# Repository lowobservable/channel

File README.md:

# channel

IBM parallel channel adapter.

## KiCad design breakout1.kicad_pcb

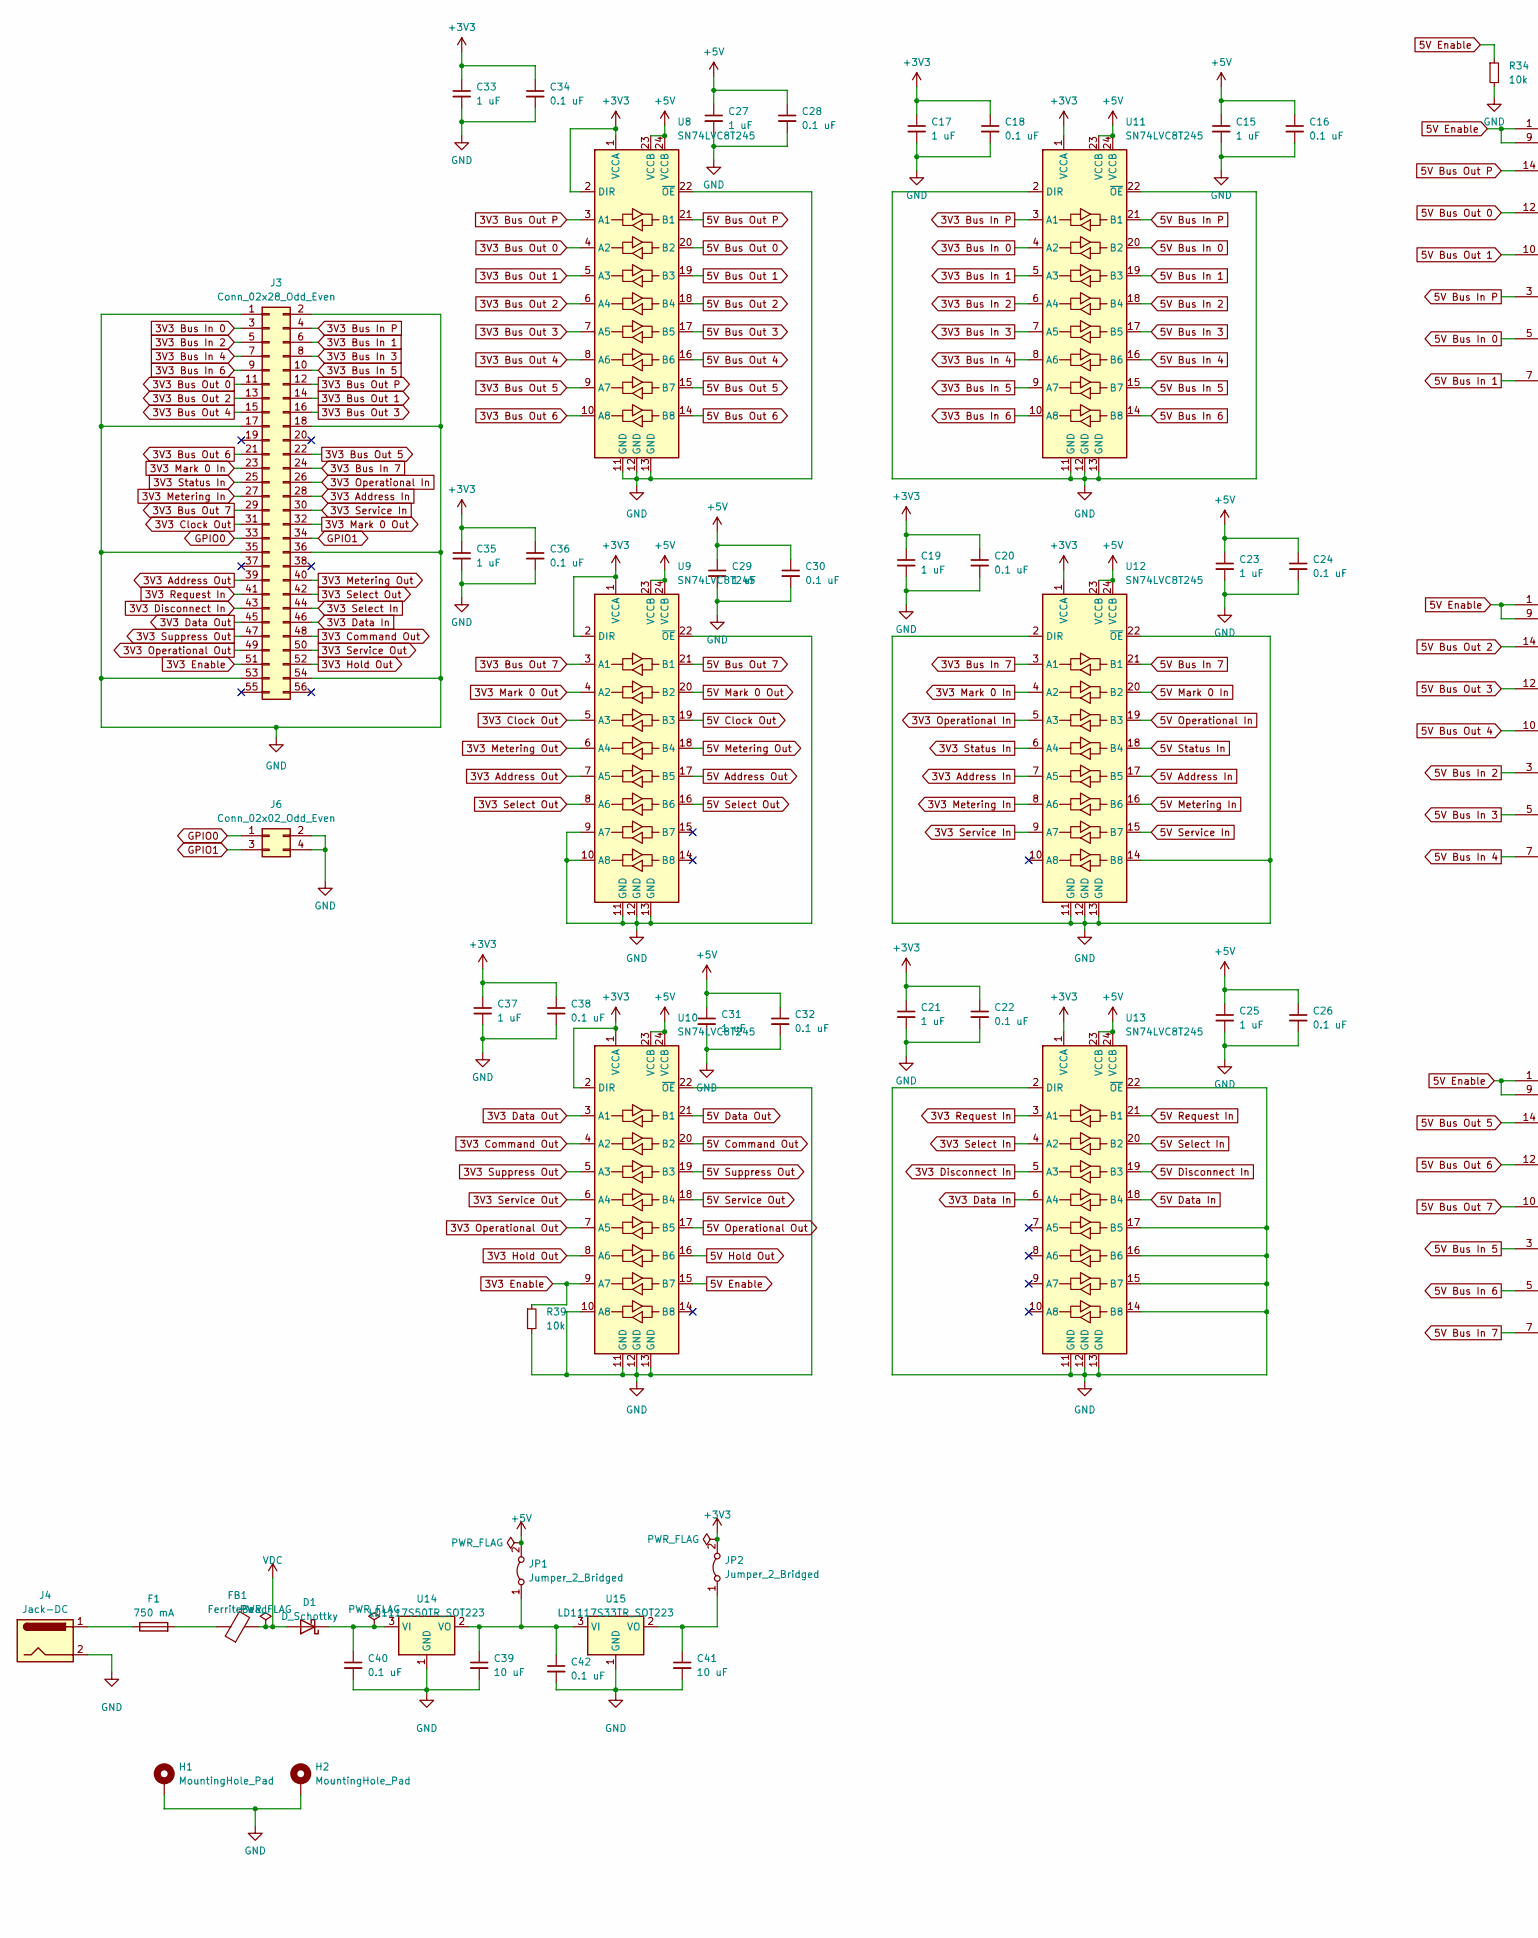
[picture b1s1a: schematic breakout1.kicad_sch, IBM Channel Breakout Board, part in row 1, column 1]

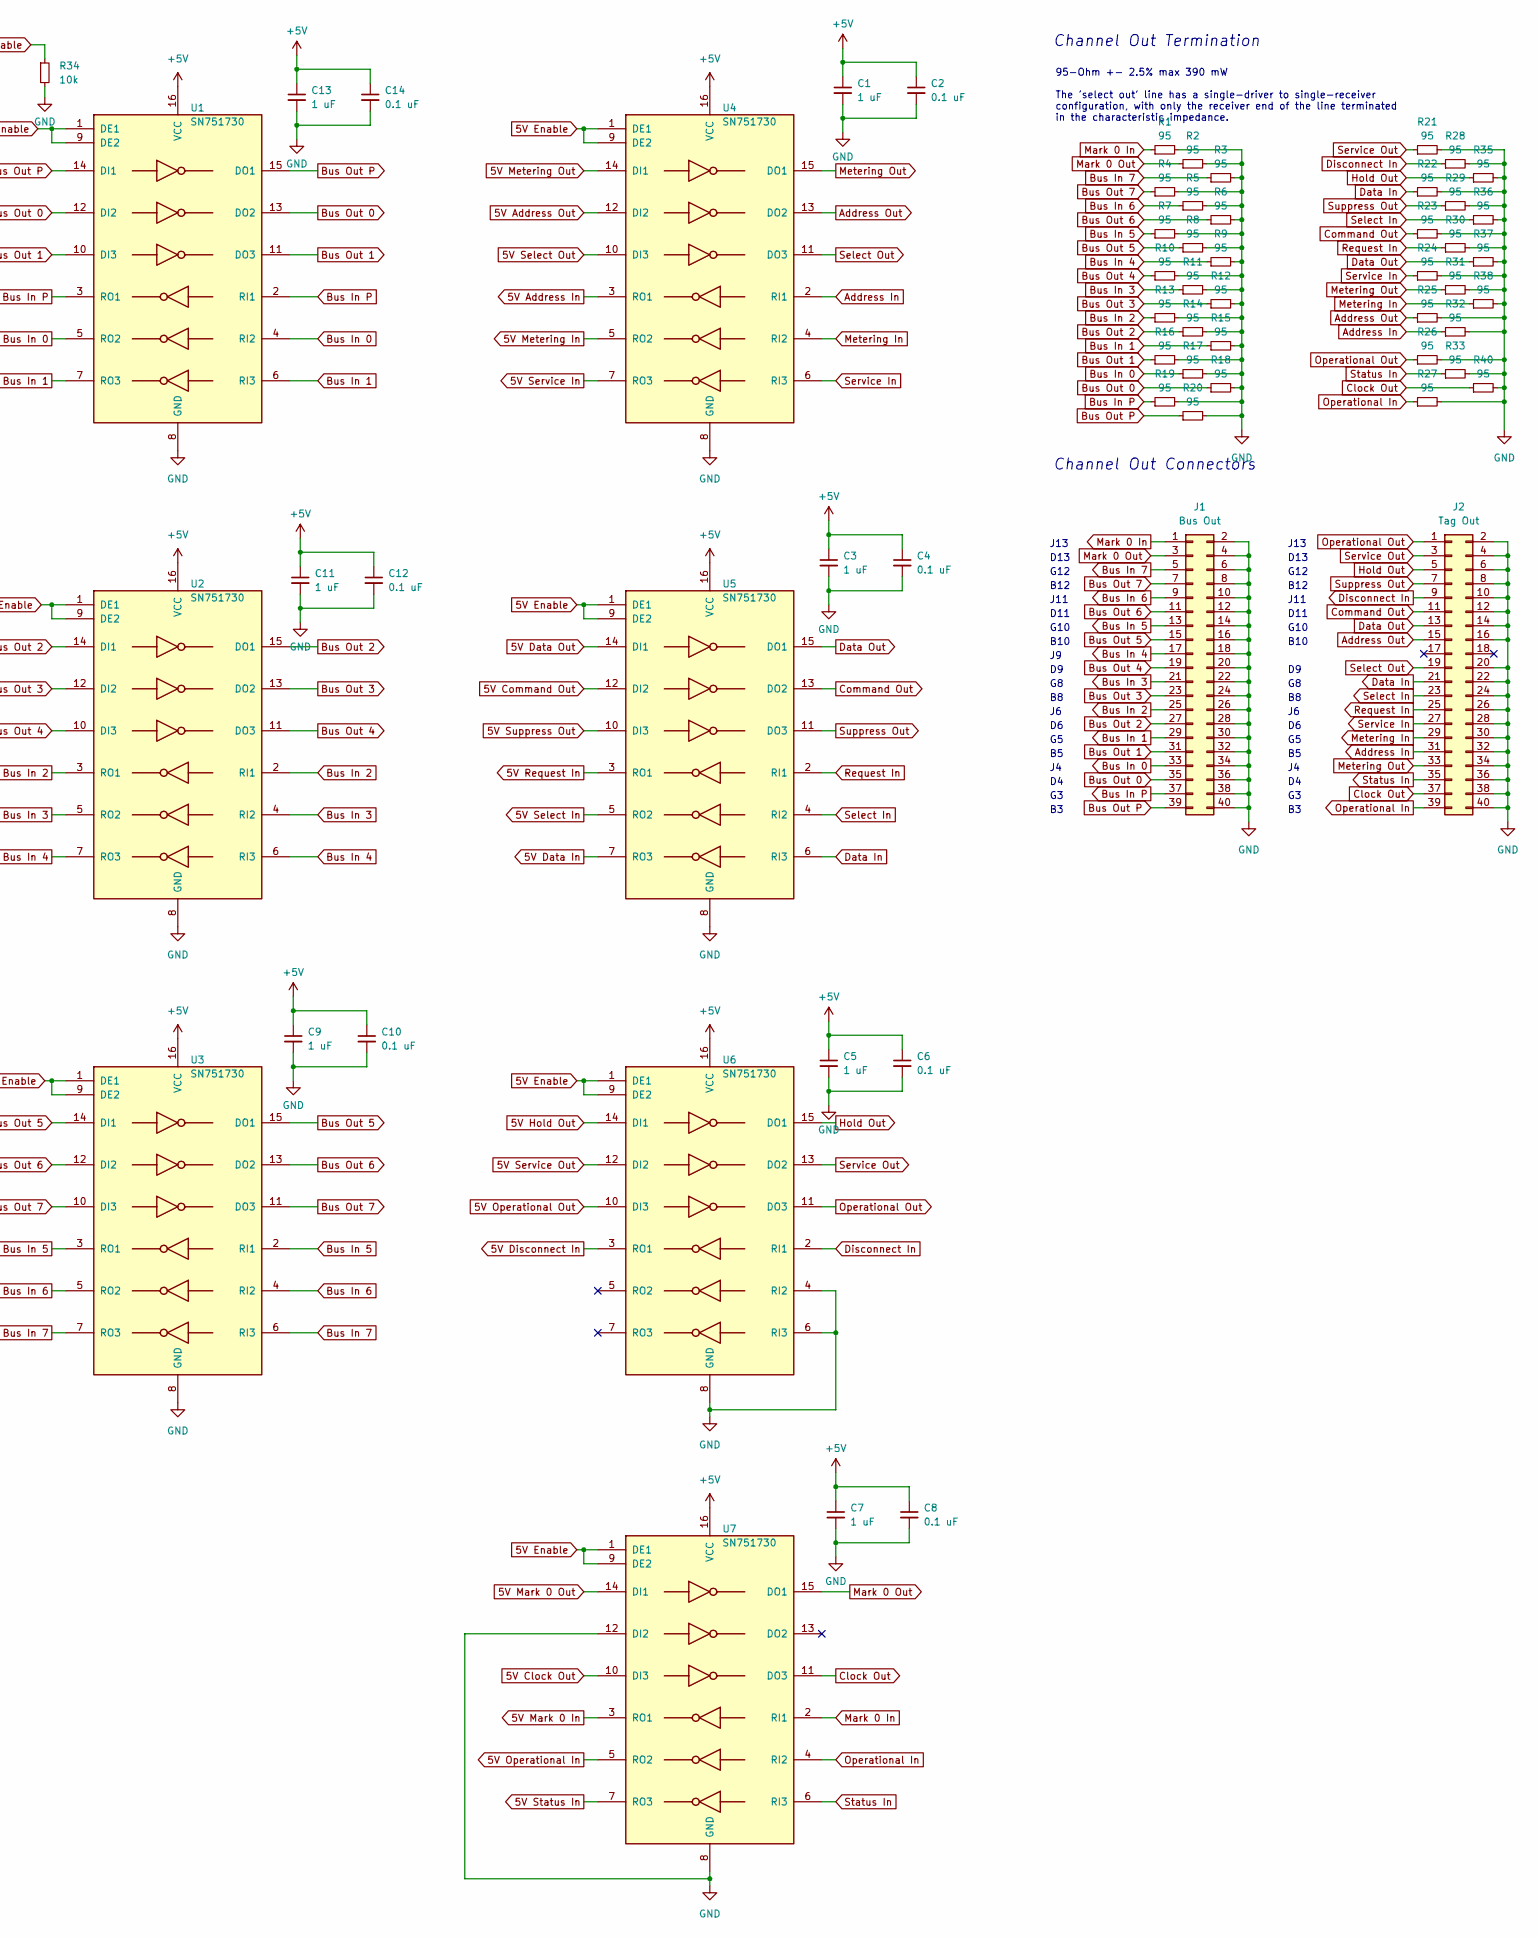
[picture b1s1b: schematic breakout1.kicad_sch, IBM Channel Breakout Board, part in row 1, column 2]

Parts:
C1, C3, C5, C7, C9, C11, C13, C15, C17, C19, C21, C23, C25, C27, C29, C31, C33, C35, C37: 1 uF; C_0603_1608Metric; Part CL10A105KP8NNNC
C2, C4, C6, C8, C10, C12, C14, C16, C18, C20, C22, C24, C26, C28, C30, C32, C34, C36, C38, C40, C42: 0.1 uF; C_0603_1608Metric; Part CL10B104KB8NNNC
C39, C41: 10 uF; C_0603_1608Metric; Part CL10A106KP8NNNC
D1: D_Schottky; D_1206_3216Metric; Part SD1206T020S1R0
F1: 750 mA; Fuse_1206_3216Metric; Part ERB-RG0R75V
FB1: FerriteBead; Fuse_1206_3216Metric; Part CZP2BPTTE101P
H1, H2: MountingHole_Pad; MountingHole_2.7mm_M2.5_ISO7380_Pad
J1: Bus Out; JST_PUD_S40B-PUDSS-1_2x20_P2.00mm_Horizontal; Part S40B-PUDSS-1
J2: Tag Out; JST_PUD_S40B-PUDSS-1_2x20_P2.00mm_Horizontal; Part S40B-PUDSS-1
J3: Conn_02x28_Odd_Even; PinSocket_2x28_P2.54mm_Vertical
J4: Jack-DC; BarrelJack_Horizontal; Part KLDX-0202-A
J6: Conn_02x02_Odd_Even; PinHeader_2x02_P2.54mm_Vertical
JP1, JP2: Jumper_2_Bridged; PinHeader_1x02_P2.54mm_Vertical
R1, R2, R3, R4, R5, R6, R7, R8, R9, R10, R11, R12, R13, R14, R15, R16, R17, R18, R19, R20, R21, R22, R23, R24, R25, R26, R27, R28, R29, R30, R31, R32, R33, R35, R36, R37, R38, R40: 95; R_0805_2012Metric; Part ERJ-P06F95R3V
R34, R39: 10k; R_0603_1608Metric; Part RC0603FR-0710KP
U1, U2, U3, U4, U5, U6, U7: SN751730; SOIC-16_3.9x9.9mm_P1.27mm; Part SN751730D
U8, U9, U10, U11, U12, U13: SN74LVC8T245; SOIC-24W_7.5x15.4mm_P1.27mm; Part SN74LVC8T245DWRG4
U14: LD1117S50TR_SOT223; SOT-223-3_TabPin2; Part LD1117S50TR
U15: LD1117S33TR_SOT223; SOT-223-3_TabPin2; Part LD1117S33TR

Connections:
3V3 Address In: J3.28, U12.7 (A5)
3V3 Address Out: J3.39, U9.7 (A5)
3V3 Bus In 0: J3.3, U11.4 (A2)
3V3 Bus In 1: J3.6, U11.5 (A3)
3V3 Bus In 2: J3.5, U11.6 (A4)
3V3 Bus In 3: J3.8, U11.7 (A5)
3V3 Bus In 4: J3.7, U11.8 (A6)
3V3 Bus In 5: J3.10, U11.9 (A7)
3V3 Bus In 6: J3.9, U11.10 (A8)
3V3 Bus In 7: J3.24, U12.3 (A1)
3V3 Bus In P: J3.4, U11.3 (A1)
3V3 Bus Out 0: J3.11, U8.4 (A2)
3V3 Bus Out 1: J3.14, U8.5 (A3)
3V3 Bus Out 2: J3.13, U8.6 (A4)
3V3 Bus Out 3: J3.16, U8.7 (A5)
3V3 Bus Out 4: J3.15, U8.8 (A6)
3V3 Bus Out 5: J3.22, U8.9 (A7)
3V3 Bus Out 6: J3.21, U8.10 (A8)
3V3 Bus Out 7: J3.29, U9.3 (A1)
3V3 Bus Out P: J3.12, U8.3 (A1)
3V3 Clock Out: J3.31, U9.5 (A3)
3V3 Command Out: J3.48, U10.4 (A2)
3V3 Data In: J3.46, U13.6 (A4)
3V3 Data Out: J3.45, U10.3 (A1)
3V3 Disconnect In: J3.43, U13.5 (A3)
3V3 Enable: J3.51, R39.1, U10.9 (A7)
3V3 Hold Out: J3.52, U10.8 (A6)
3V3 Mark 0 In: J3.23, U12.4 (A2)
3V3 Mark 0 Out: J3.32, U9.4 (A2)
3V3 Metering In: J3.27, U12.8 (A6)
3V3 Metering Out: J3.40, U9.6 (A4)
3V3 Operational In: J3.26, U12.5 (A3)
3V3 Operational Out: J3.49, U10.7 (A5)
3V3 Request In: J3.41, U13.3 (A1)
3V3 Select In: J3.44, U13.4 (A2)
3V3 Select Out: J3.42, U9.8 (A6)
3V3 Service In: J3.30, U12.9 (A7)
3V3 Service Out: J3.50, U10.6 (A4)
3V3 Status In: J3.25, U12.6 (A4)
3V3 Suppress Out: J3.47, U10.5 (A3)
5V Address In: U4.3 (RO1), U12.17 (B5)
5V Address Out: U4.12 (DI2), U9.17 (B5)
5V Bus In 0: U1.5 (RO2), U11.20 (B2)
5V Bus In 1: U1.7 (RO3), U11.19 (B3)
5V Bus In 2: U2.3 (RO1), U11.18 (B4)
5V Bus In 3: U2.5 (RO2), U11.17 (B5)
5V Bus In 4: U2.7 (RO3), U11.16 (B6)
5V Bus In 5: U3.3 (RO1), U11.15 (B7)
5V Bus In 6: U3.5 (RO2), U11.14 (B8)
5V Bus In 7: U3.7 (RO3), U12.21 (B1)
5V Bus In P: U1.3 (RO1), U11.21 (B1)
5V Bus Out 0: U1.12 (DI2), U8.20 (B2)
5V Bus Out 1: U1.10 (DI3), U8.19 (B3)
5V Bus Out 2: U2.14 (DI1), U8.18 (B4)
5V Bus Out 3: U2.12 (DI2), U8.17 (B5)
5V Bus Out 4: U2.10 (DI3), U8.16 (B6)
5V Bus Out 5: U3.14 (DI1), U8.15 (B7)
5V Bus Out 6: U3.12 (DI2), U8.14 (B8)
5V Bus Out 7: U3.10 (DI3), U9.21 (B1)
5V Bus Out P: U1.14 (DI1), U8.21 (B1)
5V Clock Out: U7.10 (DI3), U9.19 (B3)
5V Command Out: U5.12 (DI2), U10.20 (B2)
5V Data In: U5.7 (RO3), U13.18 (B4)
5V Data Out: U5.14 (DI1), U10.21 (B1)
5V Disconnect In: U6.3 (RO1), U13.19 (B3)
5V Enable: R34.1, U1.1 (DE1), U1.9 (DE2), U2.1 (DE1), U2.9 (DE2), U3.1 (DE1), U3.9 (DE2), U4.1 (DE1), U4.9 (DE2), U5.1 (DE1), U5.9 (DE2), U6.1 (DE1), U6.9 (DE2), U7.1 (DE1), U7.9 (DE2), U10.15 (B7)
5V Hold Out: U6.14 (DI1), U10.16 (B6)
5V Mark 0 In: U7.3 (RO1), U12.20 (B2)
5V Mark 0 Out: U7.14 (DI1), U9.20 (B2)
5V Metering In: U4.5 (RO2), U12.16 (B6)
5V Metering Out: U4.14 (DI1), U9.18 (B4)
5V Operational In: U7.5 (RO2), U12.19 (B3)
5V Operational Out: U6.10 (DI3), U10.17 (B5)
5V Request In: U5.3 (RO1), U13.21 (B1)
5V Select In: U5.5 (RO2), U13.20 (B2)
5V Select Out: U4.10 (DI3), U9.16 (B6)
5V Service In: U4.7 (RO3), U12.15 (B7)
5V Service Out: U6.12 (DI2), U10.18 (B4)
5V Status In: U7.7 (RO3), U12.18 (B4)
5V Suppress Out: U5.10 (DI3), U10.19 (B3)
+3V3: C17.1, C18.1, C19.1, C20.1, C21.1, C22.1, C33.1, C34.1, C35.1, C36.1, C37.1, C38.1, JP2.2 (B), U8.1 (VCCA), U8.2 (DIR), U9.1 (VCCA), U9.2 (DIR), U10.1 (VCCA), U10.2 (DIR), U11.1 (VCCA), U12.1 (VCCA), U13.1 (VCCA)
+5V: C1.1, C2.1, C3.1, C4.1, C5.1, C6.1, C7.1, C8.1, C9.1, C10.1, C11.1, C12.1, C13.1, C14.1, C15.1, C16.1, C23.1, C24.1, C25.1, C26.1, C27.1, C28.1, C29.1, C30.1, C31.1, C32.1, JP1.2 (B), U1.16 (VCC), U2.16 (VCC), U3.16 (VCC), U4.16 (VCC), U5.16 (VCC), U6.16 (VCC), U7.16 (VCC), U8.23 (VCCB), U8.24 (VCCB), U9.23 (VCCB), U9.24 (VCCB), U10.23 (VCCB), U10.24 (VCCB), U11.23 (VCCB), U11.24 (VCCB), U12.23 (VCCB), U12.24 (VCCB), U13.23 (VCCB), U13.24 (VCCB)
Address In: J2.31, R32.1, U4.2 (RI1)
Address Out: J2.15, R25.1, U4.13 (DO2)
Bus In 0: J1.33, R17.1, U1.4 (RI2)
Bus In 1: J1.29, R15.1, U1.6 (RI3)
Bus In 2: J1.25, R13.1, U2.2 (RI1)
Bus In 3: J1.21, R11.1, U2.4 (RI2)
Bus In 4: J1.17, R9.1, U2.6 (RI3)
Bus In 5: J1.13, R7.1, U3.2 (RI1)
Bus In 6: J1.9, R5.1, U3.4 (RI2)
Bus In 7: J1.5, R3.1, U3.6 (RI3)
Bus In P: J1.37, R19.1, U1.2 (RI1)
Bus Out 0: J1.35, R18.1, U1.13 (DO2)
Bus Out 1: J1.31, R16.1, U1.11 (DO3)
Bus Out 2: J1.27, R14.1, U2.15 (DO1)
Bus Out 3: J1.23, R12.1, U2.13 (DO2)
Bus Out 4: J1.19, R10.1, U2.11 (DO3)
Bus Out 5: J1.15, R8.1, U3.15 (DO1)
Bus Out 6: J1.11, R6.1, U3.13 (DO2)
Bus Out 7: J1.7, R4.1, U3.11 (DO3)
Bus Out P: J1.39, R20.1, U1.15 (DO1)
Clock Out: J2.37, R40.1, U7.11 (DO3)
Command Out: J2.11, R23.1, U5.13 (DO2)
Data In: J2.21, R22.1, U5.6 (RI3)
Data Out: J2.13, R37.1, U5.15 (DO1)
Disconnect In: J2.9, R28.1, U6.2 (RI1)
GND: C1.2, C2.2, C3.2, C4.2, C5.2, C6.2, C7.2, C8.2, C9.2, C10.2, C11.2, C12.2, C13.2, C14.2, C15.2, C16.2, C17.2, C18.2, C19.2, C20.2, C21.2, C22.2, C23.2, C24.2, C25.2, C26.2, C27.2, C28.2, C29.2, C30.2, C31.2, C32.2, C33.2, C34.2, C35.2, C36.2, C37.2, C38.2, C39.2, C40.2, C41.2, C42.2, H1.1, H2.1, J1.2, J1.4, J1.6, J1.8, J1.10, J1.12, J1.14, J1.16, J1.18, J1.20, J1.22, J1.24, J1.26, J1.28, J1.30, J1.32, J1.34, J1.36, J1.38, J1.40, J2.2, J2.4, J2.6, J2.8, J2.10, J2.12, J2.14, J2.16, J2.20, J2.22, J2.24, J2.26, J2.28, J2.30, J2.32, J2.34, J2.36, J2.38, J2.40, J3.1, J3.2, J3.17, J3.18, J3.35, J3.36, J3.53, J3.54, J4.2, J6.2, J6.4, R1.2, R2.2, R3.2, R4.2, R5.2, R6.2, R7.2, R8.2, R9.2, R10.2, R11.2, R12.2, R13.2, R14.2, R15.2, R16.2, R17.2, R18.2, R19.2, R20.2, R21.2, R22.2, R23.2, R24.2, R25.2, R26.2, R27.2, R28.2, R29.2, R30.2, R31.2, R32.2, R33.2, R34.2, R35.2, R36.2, R37.2, R38.2, R39.2, R40.2, U1.8 (GND), U2.8 (GND), U3.8 (GND), U4.8 (GND), U5.8 (GND), U6.4 (RI2), U6.6 (RI3), U6.8 (GND), U7.8 (GND), U7.12 (DI2), U8.11 (GND), U8.12 (GND), U8.13 (GND), U8.22 (~OE), U9.9 (A7), U9.10 (A8), U9.11 (GND), U9.12 (GND), U9.13 (GND), U9.22 (~OE), U10.10 (A8), U10.11 (GND), U10.12 (GND), U10.13 (GND), U10.22 (~OE), U11.2 (DIR), U11.11 (GND), U11.12 (GND), U11.13 (GND), U11.22 (~OE), U12.2 (DIR), U12.11 (GND), U12.12 (GND), U12.13 (GND), U12.14 (B8), U12.22 (~OE), U13.2 (DIR), U13.11 (GND), U13.12 (GND), U13.13 (GND), U13.14 (B8), U13.15 (B7), U13.16 (B6), U13.17 (B5), U13.22 (~OE), U14.1 (GND), U15.1 (GND)
GPIO0: J3.33, J6.1
GPIO1: J3.34, J6.3
Hold Out: J2.5, R35.1, U6.15 (DO1)
Mark 0 In: J1.1, R1.1, U7.2 (RI1)
Mark 0 Out: J1.3, R2.1, U7.15 (DO1)
Metering In: J2.29, R38.1, U4.4 (RI2)
Metering Out: J2.33, R31.1, U4.15 (DO1)
unnamed: C40.1, D1.1 (K), U14.3 (VI)
unnamed: F1.1, J4.1
unnamed: F1.2, FB1.1
unnamed: C39.1, C42.1, JP1.1 (A), U14.2 (VO), U15.3 (VI)
unnamed: C41.1, JP2.1 (A), U15.2 (VO)
Operational In: J2.39, R27.1, U7.4 (RI2)
Operational Out: J2.1, R26.1, U6.11 (DO3)
Request In: J2.25, R30.1, U5.2 (RI1)
Select In: J2.23, R36.1, U5.4 (RI2)
Select Out: J2.19, U4.11 (DO3)
Service In: J2.27, R24.1, U4.6 (RI3)
Service Out: J2.3, R21.1, U6.13 (DO2)
Status In: J2.35, R33.1, U7.6 (RI3)
Suppress Out: J2.7, R29.1, U5.11 (DO3)
VDC: D1.2 (A), FB1.2

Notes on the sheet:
95-Ohm +- 2.5% max 390 mW The 'select out' line has a single-driver to single-receiver configuration, with only the receiver end of the line terminated in the characteristic impedance.
D13
D11
J13
G12
J11
G10
Channel Out Connectors
B12
B10
Channel Out Termination

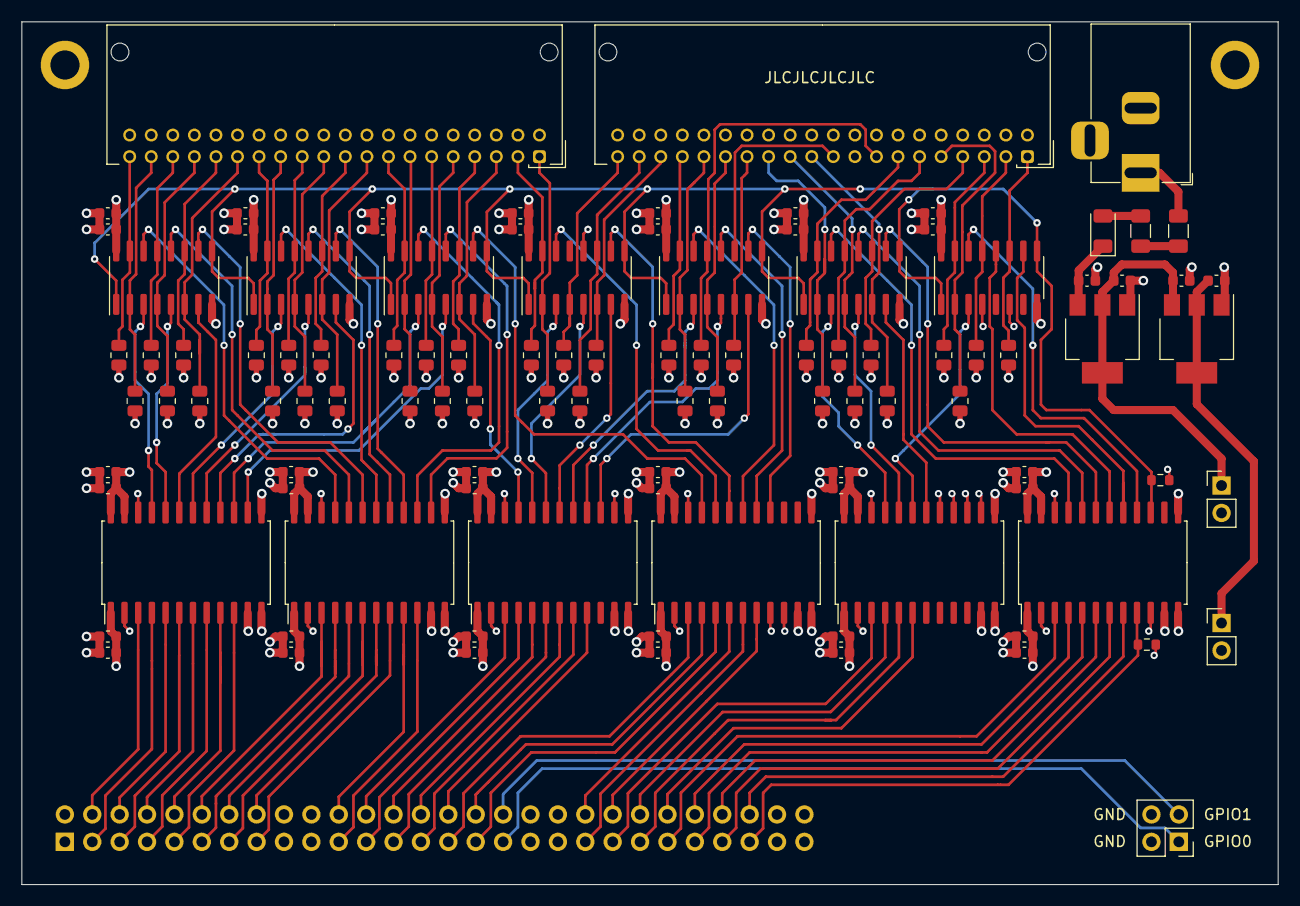
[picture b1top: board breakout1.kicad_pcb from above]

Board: 4 copper layers, 116.5 x 80.0 mm, 109 parts (1 on the bottom side), 130 nets.

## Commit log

2023-11-11 fix pinout
2024-03-26 cxip to chan for now
2024-03-26 ok I need to work on the PL now
2024-03-29 add test
2024-03-29 Add channel_tb to Vivado sim_1
2024-03-30 update lint targets
2024-03-30 linting
2024-03-30 remove unecessary semi-colon when invoking macro
2024-03-31 refactor port names, remove terminator
2024-04-01 wired up
2024-04-01 assert status and count
2024-04-05 read_command_cu_less working
2024-04-05 write_command_cu_less working
2024-04-06 read and write_command_cu_more working
2024-04-06 make order of AXI VALID and READY signals consistent
2024-04-06 refactor PS tests
2024-04-06 split constraints
2024-04-07 clean up status interface
2024-04-07 clean up registers and other misc stuff
2024-04-07 support 16-bit count
2024-04-11 quiet verilator
2024-05-21 upgrade KiCad I think
2024-05-21 update net names and XDC map
2024-06-05 set up external IO ports
2024-06-19 wrap test
2024-06-19 verilator unusedsignal warnings
2024-06-19 update pinout workbook
2024-06-19 refactor control registers and add enable bits
2024-06-20 compute and wire up parity, parity is not checked
2024-06-20 update bus mapping
2024-06-21 correct physical bus signal assignment
2024-06-22 enable drivers when frontend is enabled
2024-06-24 add condition code for not operational
2024-06-24 fix bug with termination when frontend is not enabled
2024-06-24 include request in status register
2024-06-24 fix bug with mock CU operational in being held high
2024-06-24 update chan_exec prototype to match function return type
2024-06-25 reset mock CU count when selected and add mock NOP command test
2024-06-25 add ILA
2024-06-27 bus delays for skew
2024-06-28 small changes to chan tests
2024-06-30 add short busy sequence support
2024-06-30 fix mock CU bus corruption after being selected
2024-06-30 set bus out drivers low when idle
2024-07-01 hello world
2024-07-01 very hacky read loop
2024-07-01 move prep
2024-07-01 init
2024-07-01 cleanup
2024-07-01 add some photos
2024-07-01 add connector pinout
2024-07-04 cleanup test programs
2024-07-04 change how ending status is handled
2024-07-04 run FPGA tests in GitHub actions
2024-07-04 add libhack
2024-07-06 build libchan.a
2024-07-06 add a very hacky cxip
2024-07-09 enough to connect Hercules and log into TK5
2024-07-10 fix up Hercules patch
2025-07-02 rename frontend_a to frontend_out
2025-07-02 rename channel to channel_out_protocol
2025-07-03 rename axi_channel to axi_mm_channel_out
2025-07-04 rename chan to chan_out in libchan
2025-07-06 integrate wrap test permanently
2025-07-07 copy from other branch
2025-07-08 implement system reset
2025-07-09 start work on in and out
2025-07-10 initial selection when address is not operational
2025-07-10 implement initial selection short busy sequence
2025-07-10 add 400 ms delay between address out and select out
2025-07-10 add bus in skew delay and fix short busy sequence
2025-07-12 complete initial selection
2025-07-14 read and stop
2025-07-15 write
2025-07-15 remove unecessary burst check
2025-07-15 accept ending status
2025-07-16 no requests are currently supported in selected state
2025-07-17 replace selected with connected and update operational in validation
2025-07-17 ensure channel cannot force burst mode one select out has dropped
2025-07-17 sort of an idea
2025-07-18 protocol violation error changes
2025-07-18 stack status
2025-07-18 add axi_mm_channel_out_tb
2025-07-18 read control registers
2025-07-19 write channel control register
2025-07-19 implement wrap tester
2025-07-20 cleanup protocol tests
2025-07-20 select requestor
2025-07-23 get things working together again
2025-07-23 update Vivado project
2025-07-24 disable bus in parity validation
2025-07-24 clear pending status on test
2025-07-26 not tested: move registers around
2025-07-26 start pending
2025-07-26 start - device disabled
2025-07-26 start - device not operational
2025-07-26 start - busy
2025-07-27 start - immediate command
2025-07-28 update libchan for start
2025-07-28 clean up libchan error constants
2025-07-29 update 3174-1L test
2025-08-02 stack, suppress and unstack status
2025-08-02 increase ILA sample depth
2025-08-03 data transfer
2025-08-04 update subchannel and device active after test I/O
2025-08-04 verilog linting
2025-08-04 minimal changes to cxip for latest libchan
2025-08-06 new CXIP protocol, improve Hercules device and cleanup C code
2025-08-08 remove libchan 3174-1L test
2025-08-08 add status and command format utilities
2025-08-08 improve cxip log message readability
2025-08-08 fix message corruption bug when discarding read message
2025-08-08 fix initial status handling
2025-08-08 bus in skew delay is only required if data is being received
2025-08-15 Split data message into data and count, share C protocol implementation
2025-08-15 Replace device address with device number in CXIP protocol
2025-08-21 Command chaining
2025-08-30 Use J3 and J5 for indicators
2025-09-01 Add register debug and sense ID commands to channel tool
